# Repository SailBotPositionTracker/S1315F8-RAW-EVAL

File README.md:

# S1315F8-RAW-EVAL
Carrier board for the Navspark S1315F8-RAW carrier-phase GPS module. For evaluation purposes.

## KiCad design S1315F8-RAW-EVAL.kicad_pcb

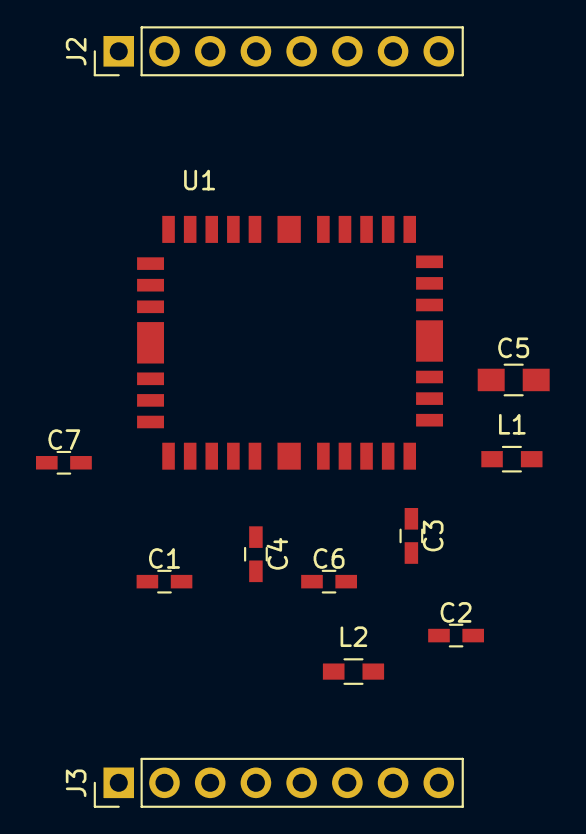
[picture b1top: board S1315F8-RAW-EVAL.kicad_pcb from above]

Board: 2 copper layers, 12 parts (0 on the bottom side), 6 nets, no tracks yet.

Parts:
C1, C2, C3, C4: .1uF; C_0603_HandSoldering
C5: 10uF; C_0805_HandSoldering
C6: 1uF; C_0603_HandSoldering
C7: 22p; C_0603_HandSoldering
J2, J3: Conn_01x08; PinHeader_1x08_P2.54mm_Vertical
L1, L2: Ferrite_Bead; L_0603_HandSoldering
U1: S1315F8-RAW

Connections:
/Receiver/VBATT+: C2.1, L2.2
/Receiver/VIN+: C1.1, L1.2
GND: C3.2, C4.2, C5.2, C6.2, U1.2, U1.3, U1.4, U1.6, U1.8, U1.9, U1.10, U1.12, U1.14, U1.15, U1.17, U1.19, U1.21, U1.22, U1.23, U1.24, U1.26, U1.28, U1.29, U1.33, U1.35, U1.36
unnamed: C3.1, C5.1, L1.1, U1.11
unnamed: C4.1, C6.1, L2.1, U1.5
unnamed: C7.2, U1.1

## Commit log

2018-11-02 first commit, added existing KiCad project
2018-11-02 added gitignore
2018-11-02 untracked previously tracked files in gitignore
